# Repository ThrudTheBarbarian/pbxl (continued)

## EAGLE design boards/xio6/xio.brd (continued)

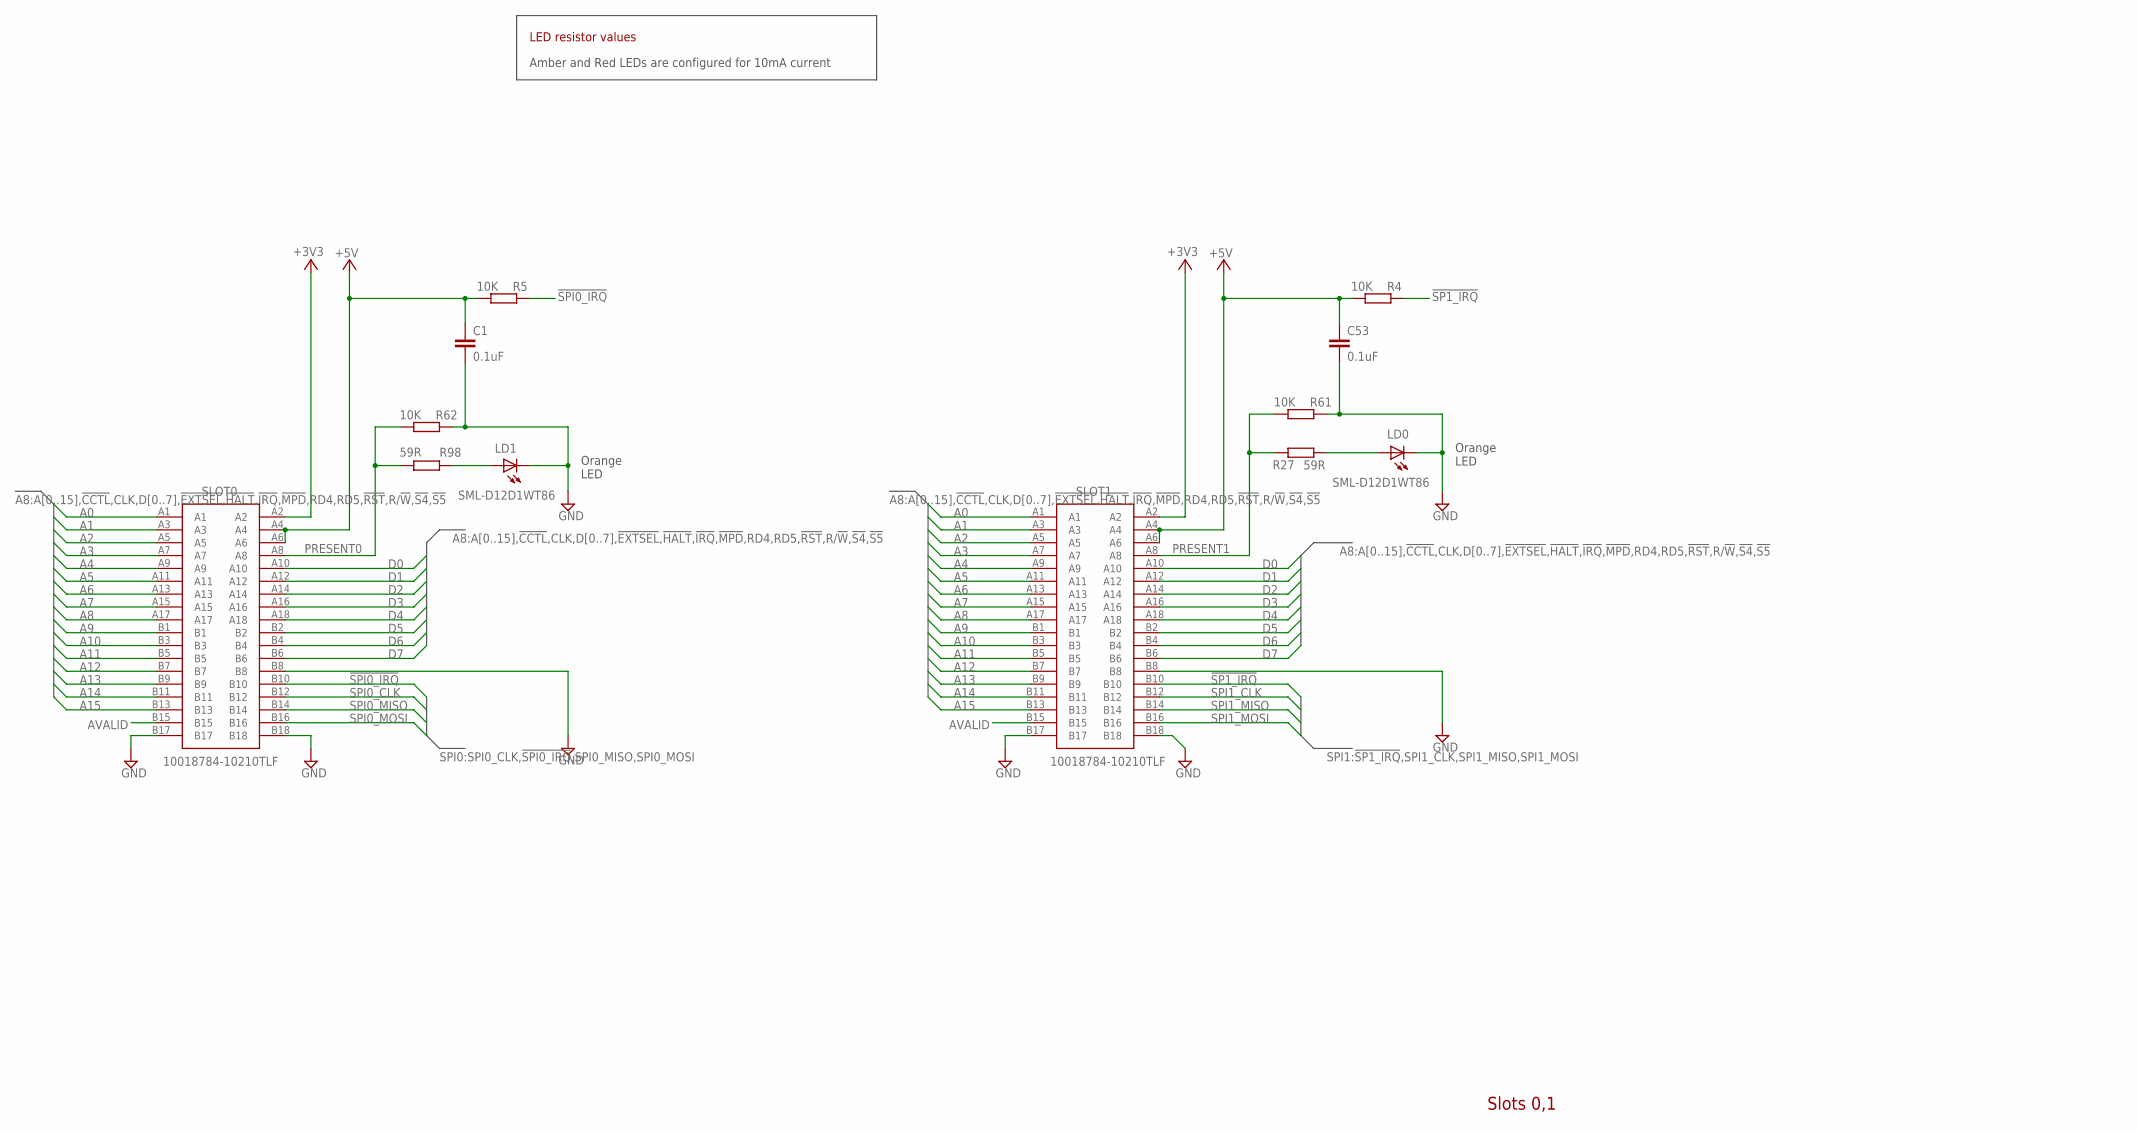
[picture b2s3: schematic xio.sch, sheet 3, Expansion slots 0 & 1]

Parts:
C1, C53: 0.1uF; C0201
LD0, LD1: SML-D12D1WT86; CHIPLED_0603
R4, R5, R61, R62: 10K; R0201
R27, R98: 59R; R0402
SLOT0, SLOT1: 10018784-10210TLF; 1001878410210TLF

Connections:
!SP1_IRQ!: R4.2, SLOT1.B10
!SPI0_IRQ!: R5.2, SLOT0.B10
+3V3: SLOT0.A2, SLOT1.A2; also elsewhere on the board
+5V: C1.1, C53.1, R4.1, R5.1, SLOT0.A4, SLOT0.A6, SLOT1.A4, SLOT1.A6; also elsewhere on the board
A0: SLOT0.A1, SLOT1.A1; also elsewhere on the board
A1: SLOT0.A3, SLOT1.A3; also elsewhere on the board
A2: SLOT0.A5, SLOT1.A5; also elsewhere on the board
A3: SLOT0.A7, SLOT1.A7; also elsewhere on the board
A4: SLOT0.A9, SLOT1.A9; also elsewhere on the board
A5: SLOT0.A11, SLOT1.A11; also elsewhere on the board
A6: SLOT0.A13, SLOT1.A13; also elsewhere on the board
A7: SLOT0.A15, SLOT1.A15; also elsewhere on the board
A8: SLOT0.A17, SLOT1.A17; also elsewhere on the board
A9: SLOT0.B1, SLOT1.B1; also elsewhere on the board
A10: SLOT0.B3, SLOT1.B3; also elsewhere on the board
A11: SLOT0.B5, SLOT1.B5; also elsewhere on the board
A12: SLOT0.B7, SLOT1.B7; also elsewhere on the board
A13: SLOT0.B9, SLOT1.B9; also elsewhere on the board
A14: SLOT0.B11, SLOT1.B11; also elsewhere on the board
A15: SLOT0.B13, SLOT1.B13; also elsewhere on the board
AVALID: SLOT0.B15, SLOT1.B15; also elsewhere on the board
D0: SLOT0.A10, SLOT1.A10; also elsewhere on the board
D1: SLOT0.A12, SLOT1.A12; also elsewhere on the board
D2: SLOT0.A14, SLOT1.A14; also elsewhere on the board
D3: SLOT0.A16, SLOT1.A16; also elsewhere on the board
D4: SLOT0.A18, SLOT1.A18; also elsewhere on the board
D5: SLOT0.B2, SLOT1.B2; also elsewhere on the board
D6: SLOT0.B4, SLOT1.B4; also elsewhere on the board
D7: SLOT0.B6, SLOT1.B6; also elsewhere on the board
GND: C1.2, C53.2, LD0.C, LD1.C, R61.2, R62.2, SLOT0.B8, SLOT0.B17, SLOT0.B18, SLOT1.B8, SLOT1.B17, SLOT1.B18; also elsewhere on the board
unnamed: LD1.A, R98.2
unnamed: LD0.A, R27.2
PRESENT0: R62.1, R98.1, SLOT0.A8
PRESENT1: R27.1, R61.1, SLOT1.A8
SPI0_CLK: SLOT0.B12
SPI0_MISO: SLOT0.B14
SPI0_MOSI: SLOT0.B16
SPI1_CLK: SLOT1.B12
SPI1_MISO: SLOT1.B14
SPI1_MOSI: SLOT1.B16

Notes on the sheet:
Slots 0,1
Orange LED
Amber and Red LEDs are configured for 10mA current
LED resistor values

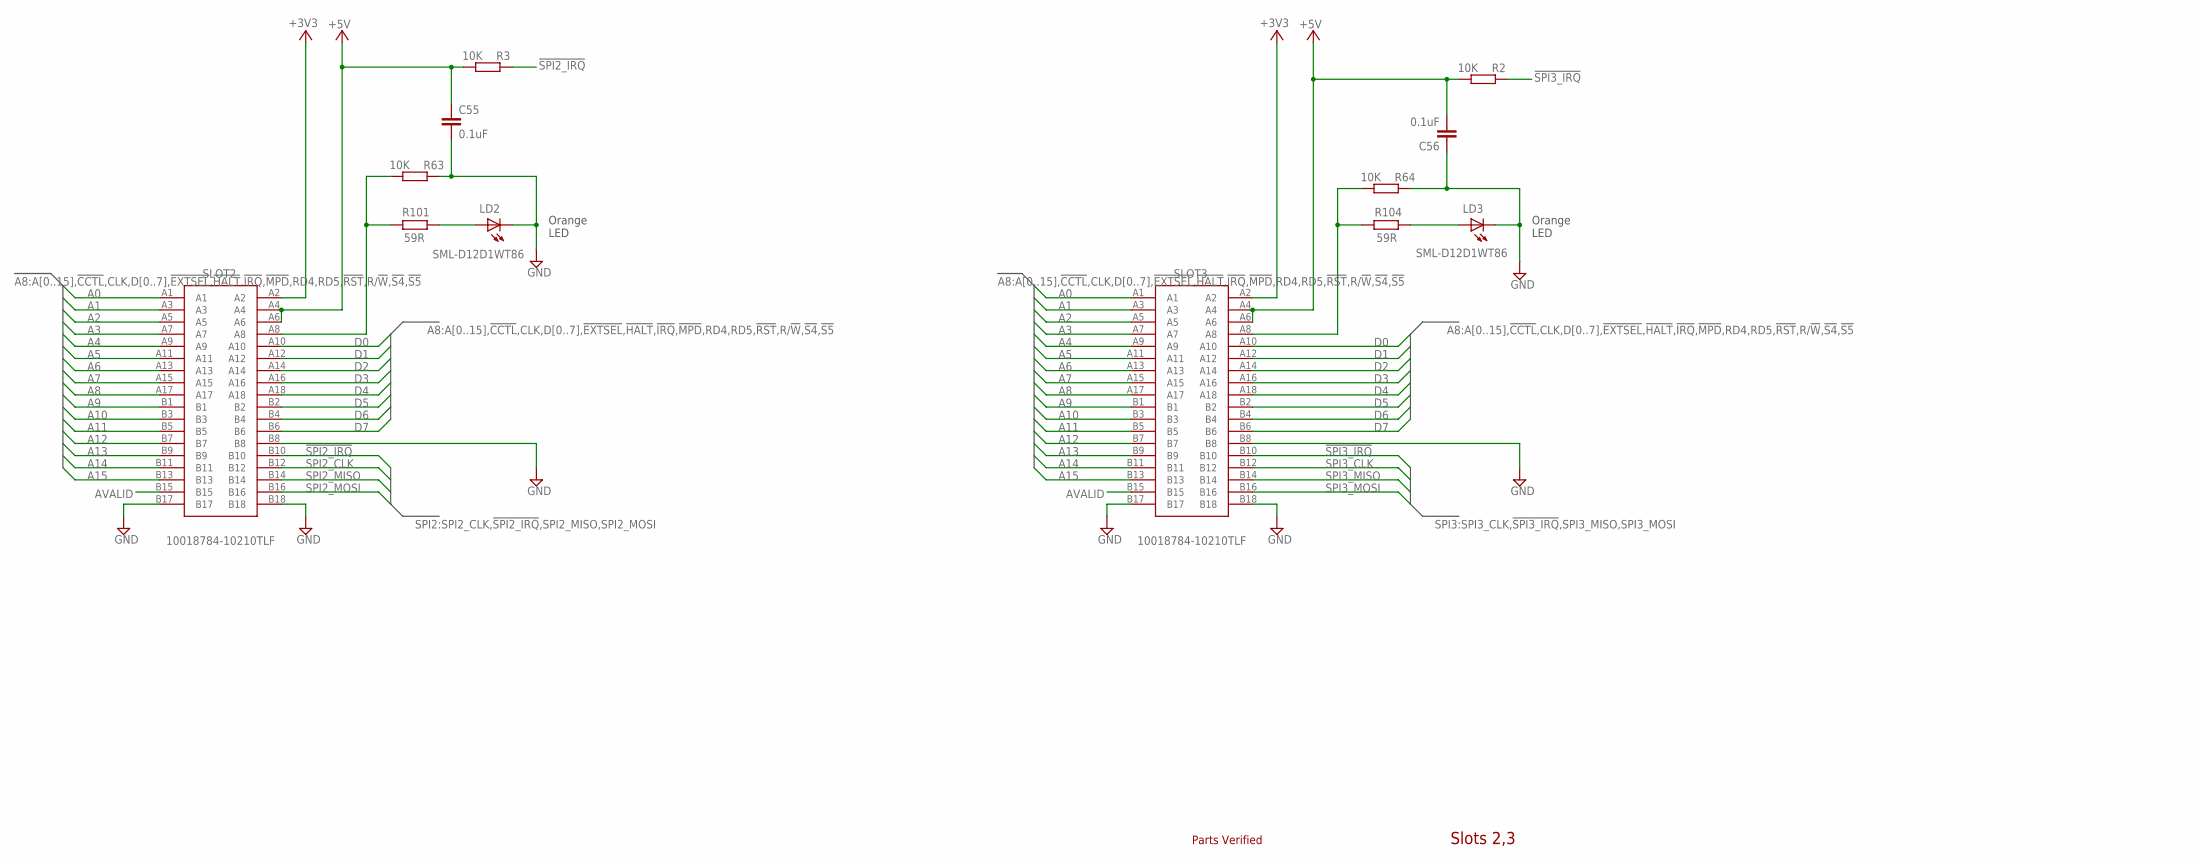
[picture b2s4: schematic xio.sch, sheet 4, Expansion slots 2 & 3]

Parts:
C55, C56: 0.1uF; C0201
LD2, LD3: SML-D12D1WT86; CHIPLED_0603
R2, R3, R63, R64: 10K; R0201
R101, R104: 59R; R0402
SLOT2, SLOT3: 10018784-10210TLF; 1001878410210TLF

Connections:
!SPI2_IRQ!: R3.2, SLOT2.B10
!SPI3_IRQ!: R2.2, SLOT3.B10
+3V3: SLOT2.A2, SLOT3.A2; also elsewhere on the board
+5V: C55.1, C56.2, R2.1, R3.1, SLOT2.A4, SLOT2.A6, SLOT3.A4, SLOT3.A6; also elsewhere on the board
A0: SLOT2.A1, SLOT3.A1; also elsewhere on the board
A1: SLOT2.A3, SLOT3.A3; also elsewhere on the board
A2: SLOT2.A5, SLOT3.A5; also elsewhere on the board
A3: SLOT2.A7, SLOT3.A7; also elsewhere on the board
A4: SLOT2.A9, SLOT3.A9; also elsewhere on the board
A5: SLOT2.A11, SLOT3.A11; also elsewhere on the board
A6: SLOT2.A13, SLOT3.A13; also elsewhere on the board
A7: SLOT2.A15, SLOT3.A15; also elsewhere on the board
A8: SLOT2.A17, SLOT3.A17; also elsewhere on the board
A9: SLOT2.B1, SLOT3.B1; also elsewhere on the board
A10: SLOT2.B3, SLOT3.B3; also elsewhere on the board
A11: SLOT2.B5, SLOT3.B5; also elsewhere on the board
A12: SLOT2.B7, SLOT3.B7; also elsewhere on the board
A13: SLOT2.B9, SLOT3.B9; also elsewhere on the board
A14: SLOT2.B11, SLOT3.B11; also elsewhere on the board
A15: SLOT2.B13, SLOT3.B13; also elsewhere on the board
AVALID: SLOT2.B15, SLOT3.B15; also elsewhere on the board
D0: SLOT2.A10, SLOT3.A10; also elsewhere on the board
D1: SLOT2.A12, SLOT3.A12; also elsewhere on the board
D2: SLOT2.A14, SLOT3.A14; also elsewhere on the board
D3: SLOT2.A16, SLOT3.A16; also elsewhere on the board
D4: SLOT2.A18, SLOT3.A18; also elsewhere on the board
D5: SLOT2.B2, SLOT3.B2; also elsewhere on the board
D6: SLOT2.B4, SLOT3.B4; also elsewhere on the board
D7: SLOT2.B6, SLOT3.B6; also elsewhere on the board
GND: C55.2, C56.1, LD2.C, LD3.C, R63.2, R64.2, SLOT2.B8, SLOT2.B17, SLOT2.B18, SLOT3.B8, SLOT3.B17, SLOT3.B18; also elsewhere on the board
unnamed: LD2.A, R101.2
unnamed: R64.1, R104.1, SLOT3.A8
unnamed: R63.1, R101.1, SLOT2.A8
unnamed: LD3.A, R104.2
SPI2_CLK: SLOT2.B12
SPI2_MISO: SLOT2.B14
SPI2_MOSI: SLOT2.B16
SPI3_CLK: SLOT3.B12
SPI3_MISO: SLOT3.B14
SPI3_MOSI: SLOT3.B16

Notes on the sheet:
Slots 2,3
Orange LED
Parts Verified

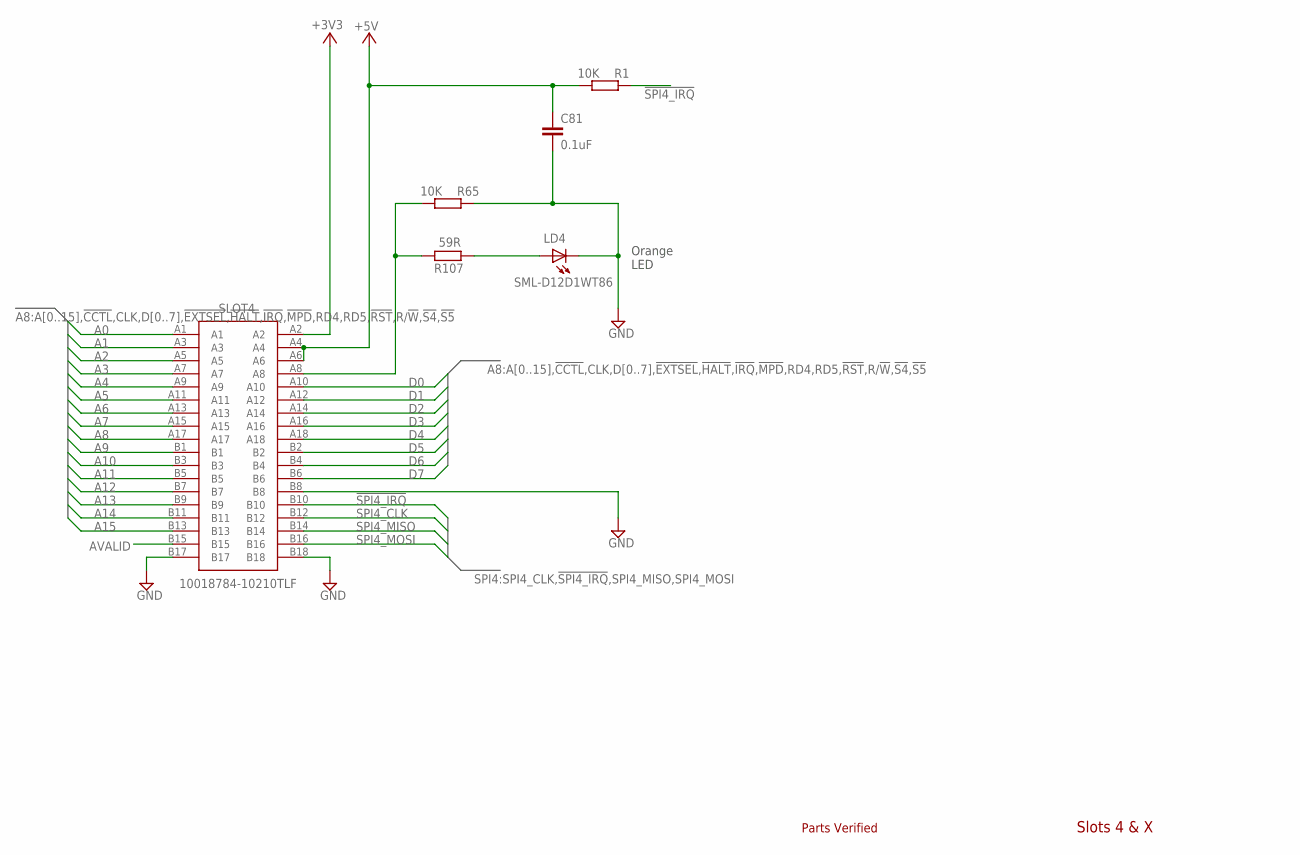
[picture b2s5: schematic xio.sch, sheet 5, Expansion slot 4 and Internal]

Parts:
C81: 0.1uF; C0201
LD4: SML-D12D1WT86; CHIPLED_0603
R1, R65: 10K; R0201
R107: 59R; R0402
SLOT4: 10018784-10210TLF; 1001878410210TLF

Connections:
!SPI4_IRQ!: R1.2, SLOT4.B10
+3V3: SLOT4.A2; also elsewhere on the board
+5V: C81.1, R1.1, SLOT4.A4, SLOT4.A6; also elsewhere on the board
A0: SLOT4.A1; also elsewhere on the board
A1: SLOT4.A3; also elsewhere on the board
A2: SLOT4.A5; also elsewhere on the board
A3: SLOT4.A7; also elsewhere on the board
A4: SLOT4.A9; also elsewhere on the board
A5: SLOT4.A11; also elsewhere on the board
A6: SLOT4.A13; also elsewhere on the board
A7: SLOT4.A15; also elsewhere on the board
A8: SLOT4.A17; also elsewhere on the board
A9: SLOT4.B1; also elsewhere on the board
A10: SLOT4.B3; also elsewhere on the board
A11: SLOT4.B5; also elsewhere on the board
A12: SLOT4.B7; also elsewhere on the board
A13: SLOT4.B9; also elsewhere on the board
A14: SLOT4.B11; also elsewhere on the board
A15: SLOT4.B13; also elsewhere on the board
AVALID: SLOT4.B15; also elsewhere on the board
D0: SLOT4.A10; also elsewhere on the board
D1: SLOT4.A12; also elsewhere on the board
D2: SLOT4.A14; also elsewhere on the board
D3: SLOT4.A16; also elsewhere on the board
D4: SLOT4.A18; also elsewhere on the board
D5: SLOT4.B2; also elsewhere on the board
D6: SLOT4.B4; also elsewhere on the board
D7: SLOT4.B6; also elsewhere on the board
GND: C81.2, LD4.C, R65.2, SLOT4.B8, SLOT4.B17, SLOT4.B18; also elsewhere on the board
unnamed: R65.1, R107.1, SLOT4.A8
unnamed: LD4.A, R107.2
SPI4_CLK: SLOT4.B12
SPI4_MISO: SLOT4.B14
SPI4_MOSI: SLOT4.B16

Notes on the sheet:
Slots 4 & X
Orange LED
Parts Verified

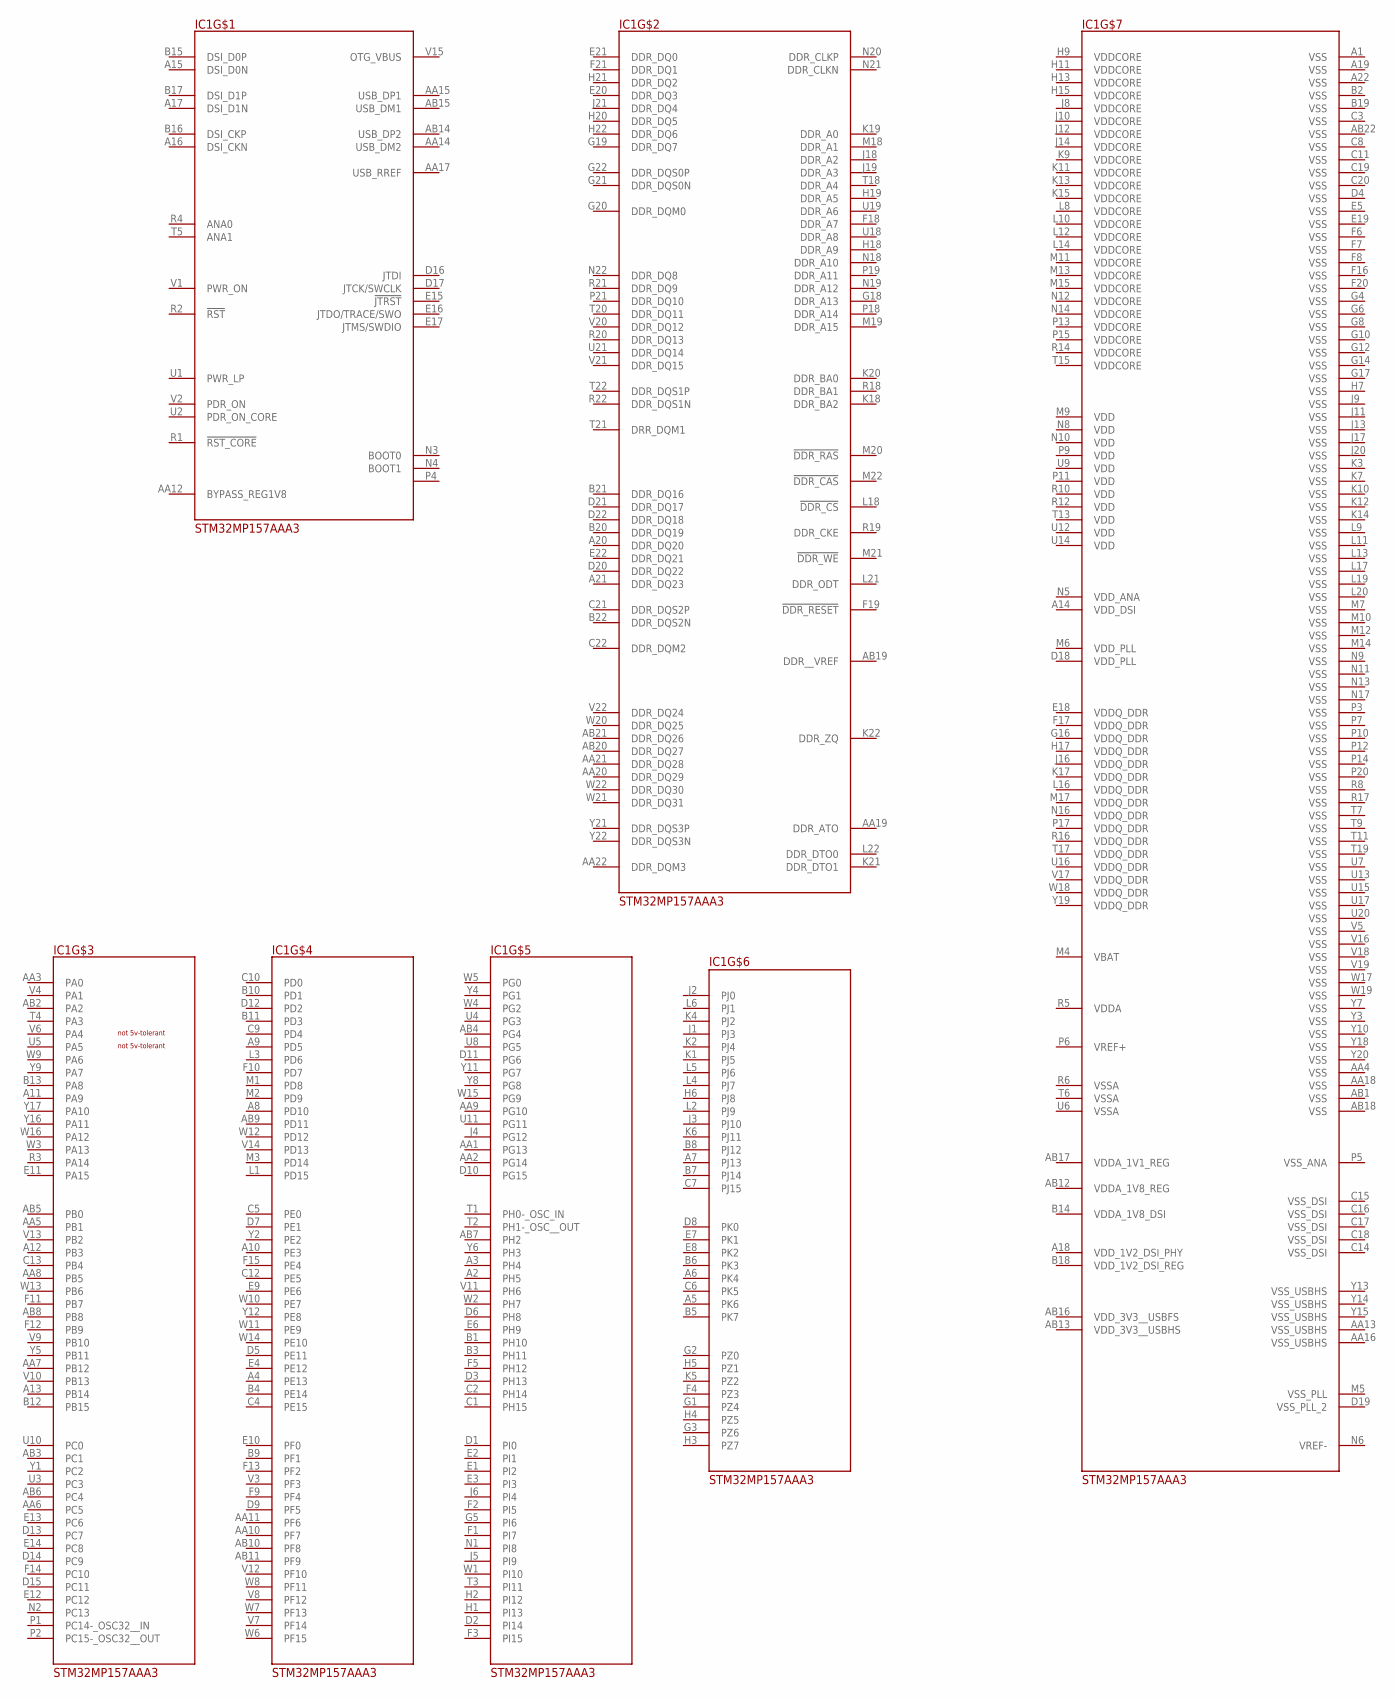
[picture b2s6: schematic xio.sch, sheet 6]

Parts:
IC1: STM32MP157AAA3; BGA448C80P22X22_1800X1800X127

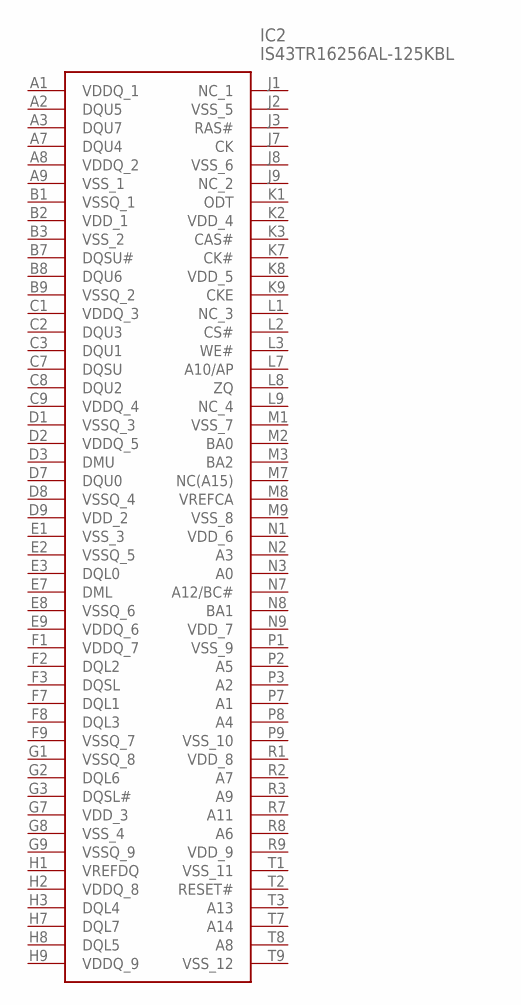
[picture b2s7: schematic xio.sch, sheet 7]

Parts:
IC2: IS43TR16256AL-125KBL; BGA96C80P9X16_900X1300X120

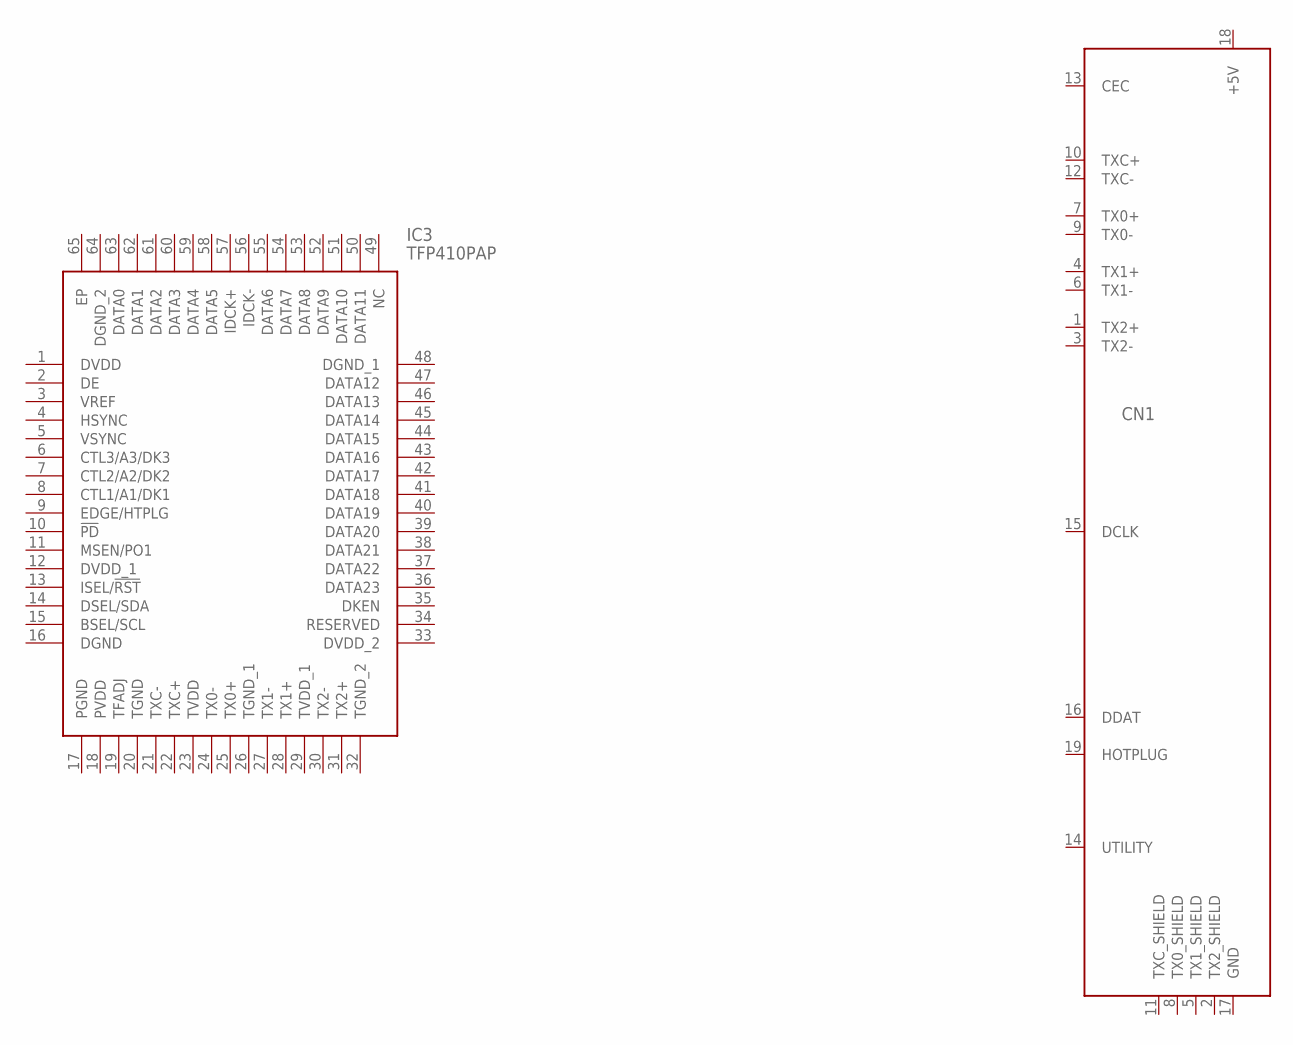
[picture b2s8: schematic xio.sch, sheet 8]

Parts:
CN1: HDMI_MOLEX_47151-0001
IC3: TFP410PAP; QFP50P1200X1200X120-65N

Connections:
+5V: CN1.18 (+5V); also elsewhere on the board
DGND: IC3.16 (DGND)
DGND_1: IC3.48 (DGND_1)
DGND_2: IC3.64 (DGND_2)
DVDD: IC3.1 (DVDD)
DVDD_1: IC3.12 (DVDD_1)
DVDD_2: IC3.33 (DVDD_2)
GND: CN1.17 (GND), CN1.P$1 (GND), CN1.P$2 (GND), CN1.P$3 (GND), CN1.P$4 (GND); also elsewhere on the board
PGND: IC3.17 (PGND)
PVDD: IC3.18 (PVDD)
TGND: IC3.20 (TGND)
TGND_1: IC3.26 (TGND_1)
TGND_2: IC3.32 (TGND_2)
TVDD: IC3.23 (TVDD)
TVDD_1: IC3.29 (TVDD_1)
TX0_SHIELD: CN1.8 (TX0_SHIELD)
TX1_SHIELD: CN1.5 (TX1_SHIELD)
TX2_SHIELD: CN1.2 (TX2_SHIELD)
TXC_SHIELD: CN1.11 (TXC_SHIELD)

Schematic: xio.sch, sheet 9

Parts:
J3: RJMG2310228A0ER

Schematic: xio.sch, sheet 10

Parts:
J1: DC-005; DCJ3P-14.2X11.0X9.0MM

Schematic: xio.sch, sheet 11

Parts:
IC4: STPMIC1APQR; QFN40P500X600X80-45N

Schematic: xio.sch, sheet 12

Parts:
J2: MICROSD_MOLEX_5025700893; 5025700893

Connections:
SH1: J2.GND0 (SH1)
SH2: J2.GND1 (SH2)
SH3: J2.GND2 (SH3)
SH4: J2.GND3 (SH4)
SH5: J2.GND4 (SH5)
VDD: J2.P$4 (VDD)
VSS: J2.P$6 (VSS)

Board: 4 copper layers, 40 parts (0 on the bottom side), 55 nets, no tracks yet.

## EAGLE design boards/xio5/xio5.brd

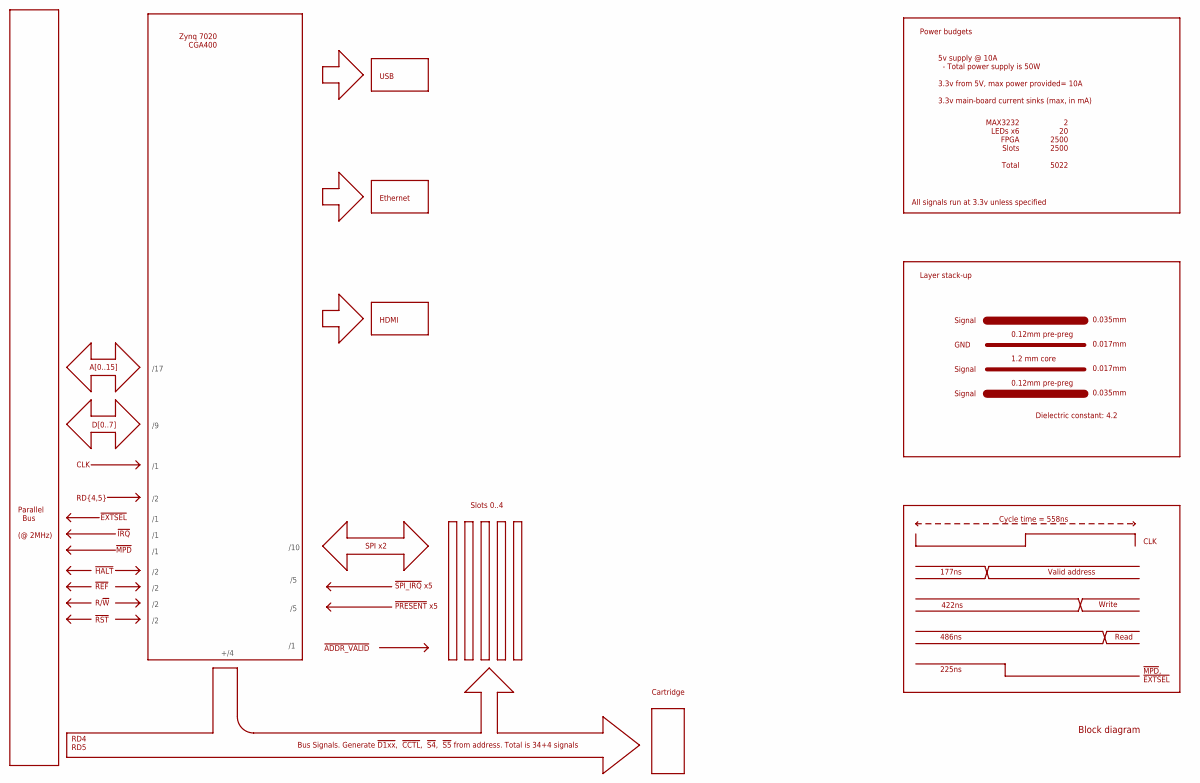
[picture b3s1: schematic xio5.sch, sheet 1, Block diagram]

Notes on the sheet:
Slots 0..4
Bus Signals. Generate !D1xx!, !CCTL!, !S4!, !S5! from address. Total is 34+4 signals
5v supply @ 10A - Total power supply is 50W 3.3v from 5V, max power provided= 10A 3.3v main-board current sinks (max, in mA)
MAX3232 LEDs x6 FPGA Slots Total
2 20 2500 2500 5022
1.2 mm core
0.12mm pre-preg
0.035mm
0.017mm
Layer stack-up
GND
Dielectric constant: 4.2
Cycle time = 558ns
Valid address
Write
Read
177ns
422ns
486ns
225ns
!MPD!, !EXTSEL!
CLK
Power budgets
Zynq 7020 CGA400
HDMI
Signal
Block diagram
Parallel Bus (@ 2MHz)
A[0..15]
D[0..7]
RD{4,5}
!MPD!
!IRQ!
!EXTSEL!
!HALT!
!REF!
R/!W!
/17
!ADDR_VALID!
+/4

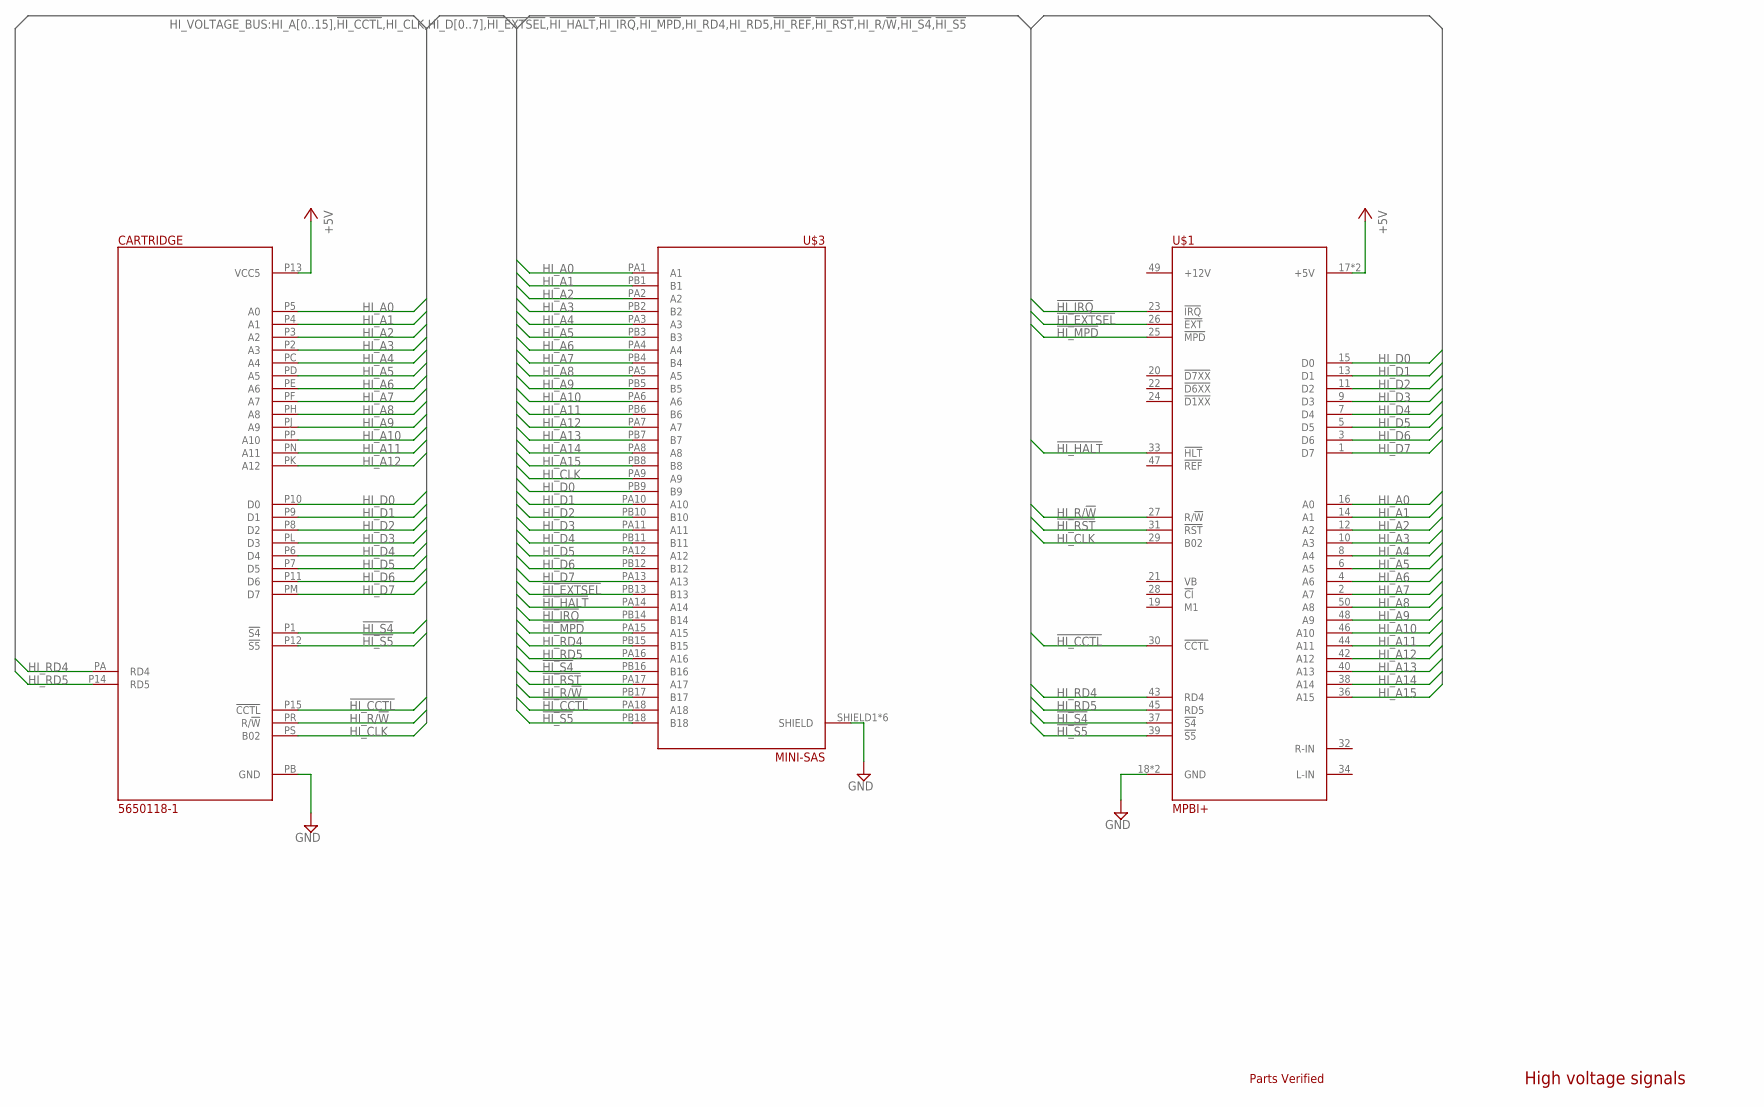
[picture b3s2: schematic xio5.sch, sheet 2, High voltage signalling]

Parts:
CARTRIDGE: 5650118-1; A8_CART
U$1: MPBI+; 2X25
U$3: MINI-SAS

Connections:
!HI_CCTL!: CARTRIDGE.P15 (!CCTL!), U$1.30 (!CCTL!), U$3.PA18 (A18)
!HI_EXTSEL!: U$1.26 (!EXT!), U$3.PB13 (B13); also elsewhere on the board
!HI_HALT!: U$1.33 (!HLT!), U$3.PA14 (A14); also elsewhere on the board
!HI_IRQ!: U$1.23 (!IRQ!), U$3.PB14 (B14); also elsewhere on the board
!HI_MPD!: U$1.25 (!MPD!), U$3.PA15 (A15); also elsewhere on the board
!HI_RST!: U$1.31 (!RST!), U$3.PA17 (A17); also elsewhere on the board
!HI_S4!: CARTRIDGE.P1 (!S4!), U$1.37 (!S4!), U$3.PB16 (B16)
!HI_S5!: CARTRIDGE.P12 (!S5!), U$1.39 (!S5!), U$3.PB18 (B18)
+5V: CARTRIDGE.P13 (VCC5), U$1.17 (+5V), U$1.41 (+5V); also elsewhere on the board
GND: CARTRIDGE.PB (GND), U$1.18 (GND), U$1.35 (GND), U$3.SHIELD1 (SHIELD), U$3.SHIELD2 (SHIELD), U$3.SHIELD3 (SHIELD), U$3.SHIELD4 (SHIELD), U$3.SHIELD5 (SHIELD), U$3.SHIELD6 (SHIELD); also elsewhere on the board
HI_A0: CARTRIDGE.P5 (A0), U$1.16 (A0), U$3.PA1 (A1); also elsewhere on the board
HI_A1: CARTRIDGE.P4 (A1), U$1.14 (A1), U$3.PB1 (B1); also elsewhere on the board
HI_A2: CARTRIDGE.P3 (A2), U$1.12 (A2), U$3.PA2 (A2); also elsewhere on the board
HI_A3: CARTRIDGE.P2 (A3), U$1.10 (A3), U$3.PB2 (B2); also elsewhere on the board
HI_A4: CARTRIDGE.PC (A4), U$1.8 (A4), U$3.PA3 (A3); also elsewhere on the board
HI_A5: CARTRIDGE.PD (A5), U$1.6 (A5), U$3.PB3 (B3); also elsewhere on the board
HI_A6: CARTRIDGE.PE (A6), U$1.4 (A6), U$3.PA4 (A4); also elsewhere on the board
HI_A7: CARTRIDGE.PF (A7), U$1.2 (A7), U$3.PB4 (B4); also elsewhere on the board
HI_A8: CARTRIDGE.PH (A8), U$1.50 (A8), U$3.PA5 (A5); also elsewhere on the board
HI_A9: CARTRIDGE.PJ (A9), U$1.48 (A9), U$3.PB5 (B5); also elsewhere on the board
HI_A10: CARTRIDGE.PP (A10), U$1.46 (A10), U$3.PA6 (A6); also elsewhere on the board
HI_A11: CARTRIDGE.PN (A11), U$1.44 (A11), U$3.PB6 (B6); also elsewhere on the board
HI_A12: CARTRIDGE.PK (A12), U$1.42 (A12), U$3.PA7 (A7); also elsewhere on the board
HI_A13: U$1.40 (A13), U$3.PB7 (B7); also elsewhere on the board
HI_A14: U$1.38 (A14), U$3.PA8 (A8); also elsewhere on the board
HI_A15: U$1.36 (A15), U$3.PB8 (B8); also elsewhere on the board
HI_CLK: CARTRIDGE.PS (B02), U$1.29 (B02), U$3.PA9 (A9); also elsewhere on the board
HI_D0: CARTRIDGE.P10 (D0), U$1.15 (D0), U$3.PB9 (B9); also elsewhere on the board
HI_D1: CARTRIDGE.P9 (D1), U$1.13 (D1), U$3.PA10 (A10); also elsewhere on the board
HI_D2: CARTRIDGE.P8 (D2), U$1.11 (D2), U$3.PB10 (B10); also elsewhere on the board
HI_D3: CARTRIDGE.PL (D3), U$1.9 (D3), U$3.PA11 (A11); also elsewhere on the board
HI_D4: CARTRIDGE.P6 (D4), U$1.7 (D4), U$3.PB11 (B11); also elsewhere on the board
HI_D5: CARTRIDGE.P7 (D5), U$1.5 (D5), U$3.PA12 (A12); also elsewhere on the board
HI_D6: CARTRIDGE.P11 (D6), U$1.3 (D6), U$3.PB12 (B12); also elsewhere on the board
HI_D7: CARTRIDGE.PM (D7), U$1.1 (D7), U$3.PA13 (A13); also elsewhere on the board
HI_R/!W!: CARTRIDGE.PR (R/!W!), U$1.27 (R/!W!), U$3.PB17 (B17); also elsewhere on the board
HI_RD4: CARTRIDGE.PA (RD4), U$1.43 (RD4), U$3.PB15 (B15); also elsewhere on the board
HI_RD5: CARTRIDGE.P14 (RD5), U$1.45 (RD5), U$3.PA16 (A16); also elsewhere on the board

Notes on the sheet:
High voltage signals
Parts Verified
